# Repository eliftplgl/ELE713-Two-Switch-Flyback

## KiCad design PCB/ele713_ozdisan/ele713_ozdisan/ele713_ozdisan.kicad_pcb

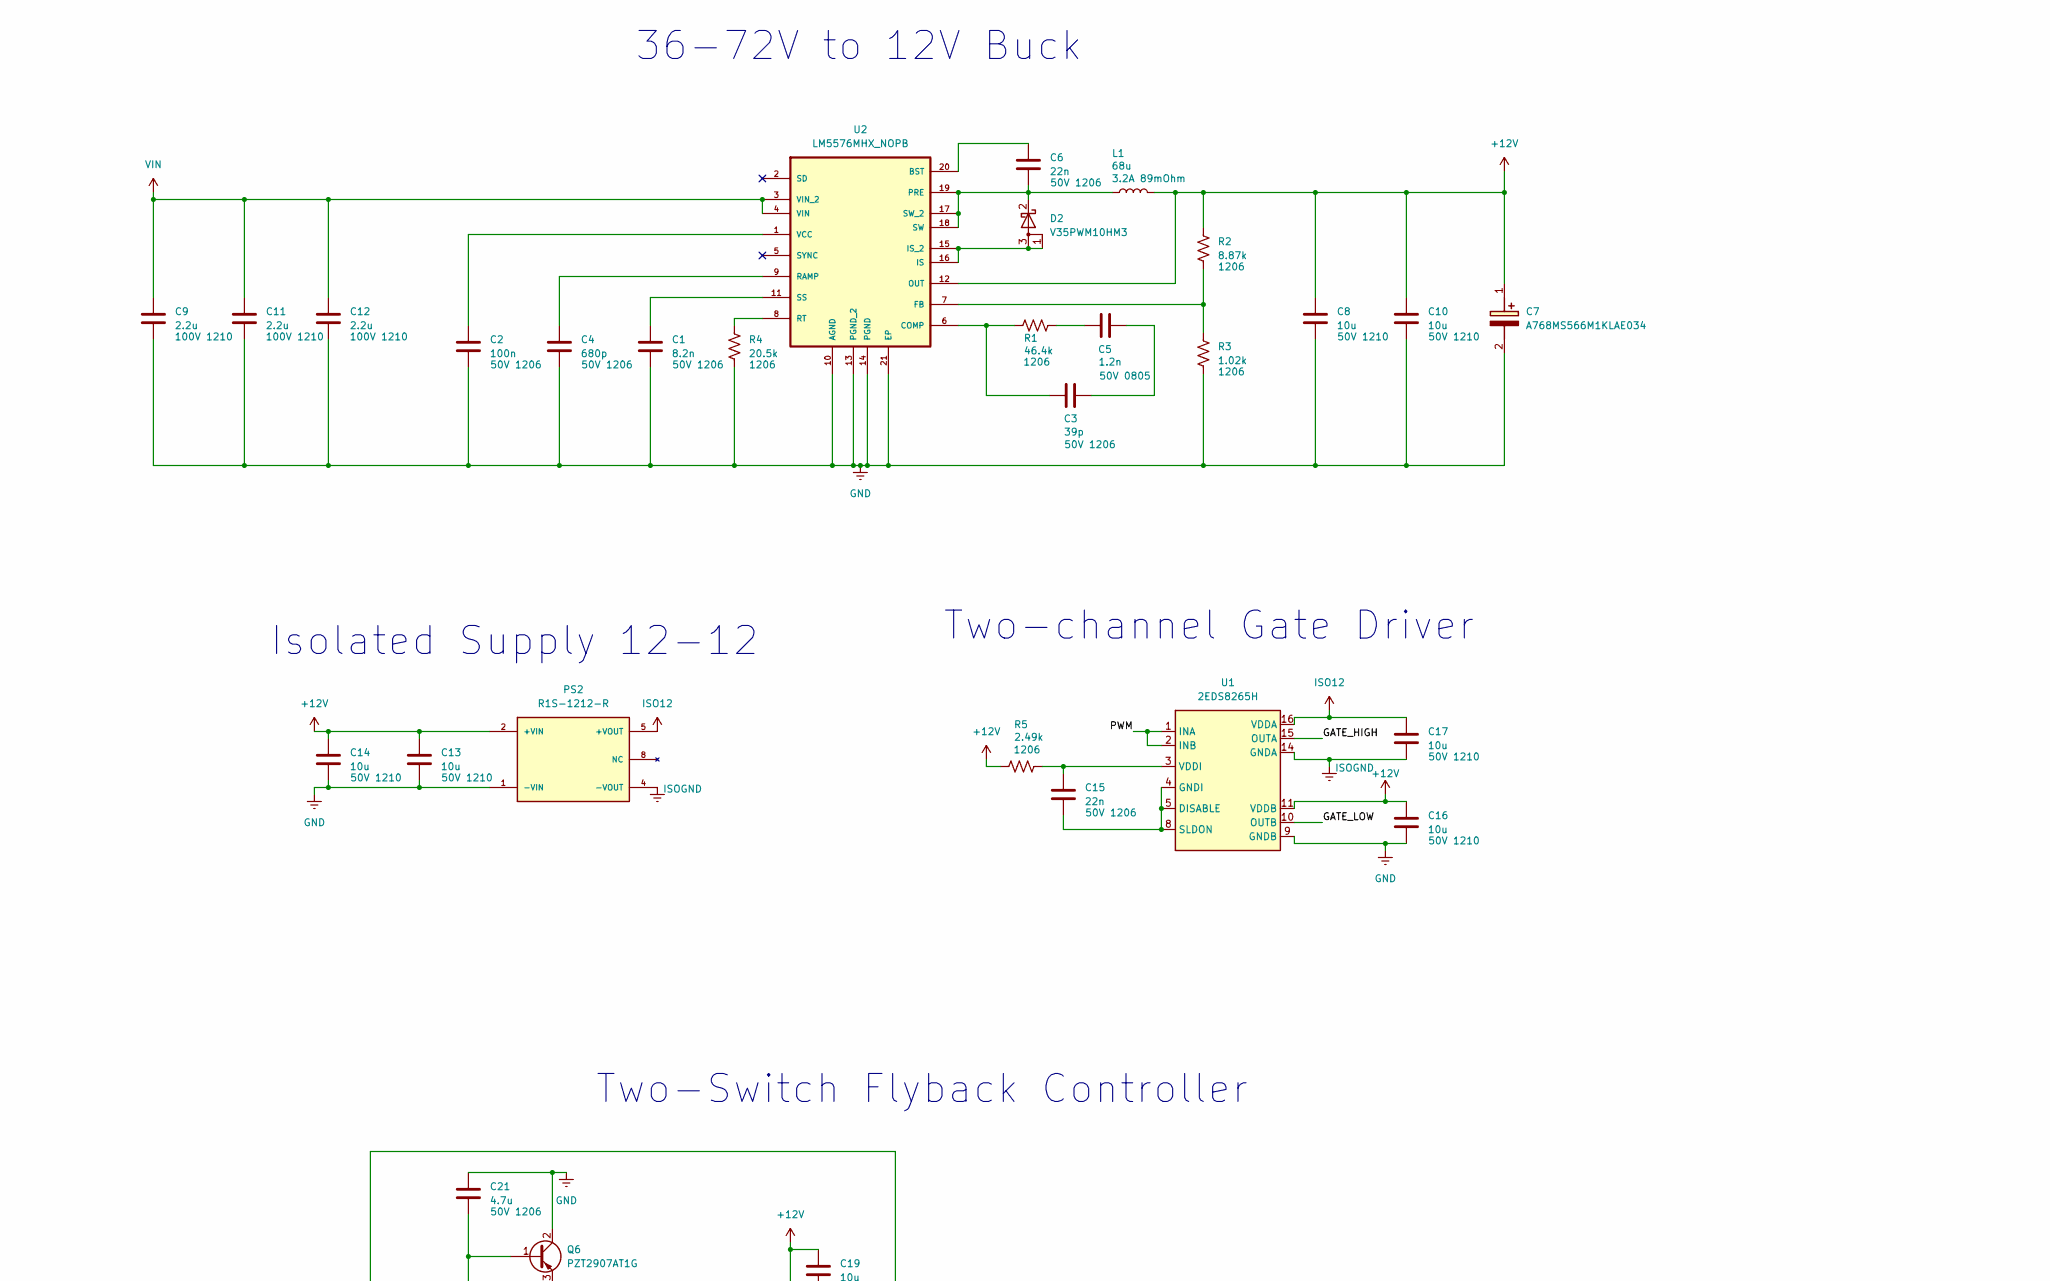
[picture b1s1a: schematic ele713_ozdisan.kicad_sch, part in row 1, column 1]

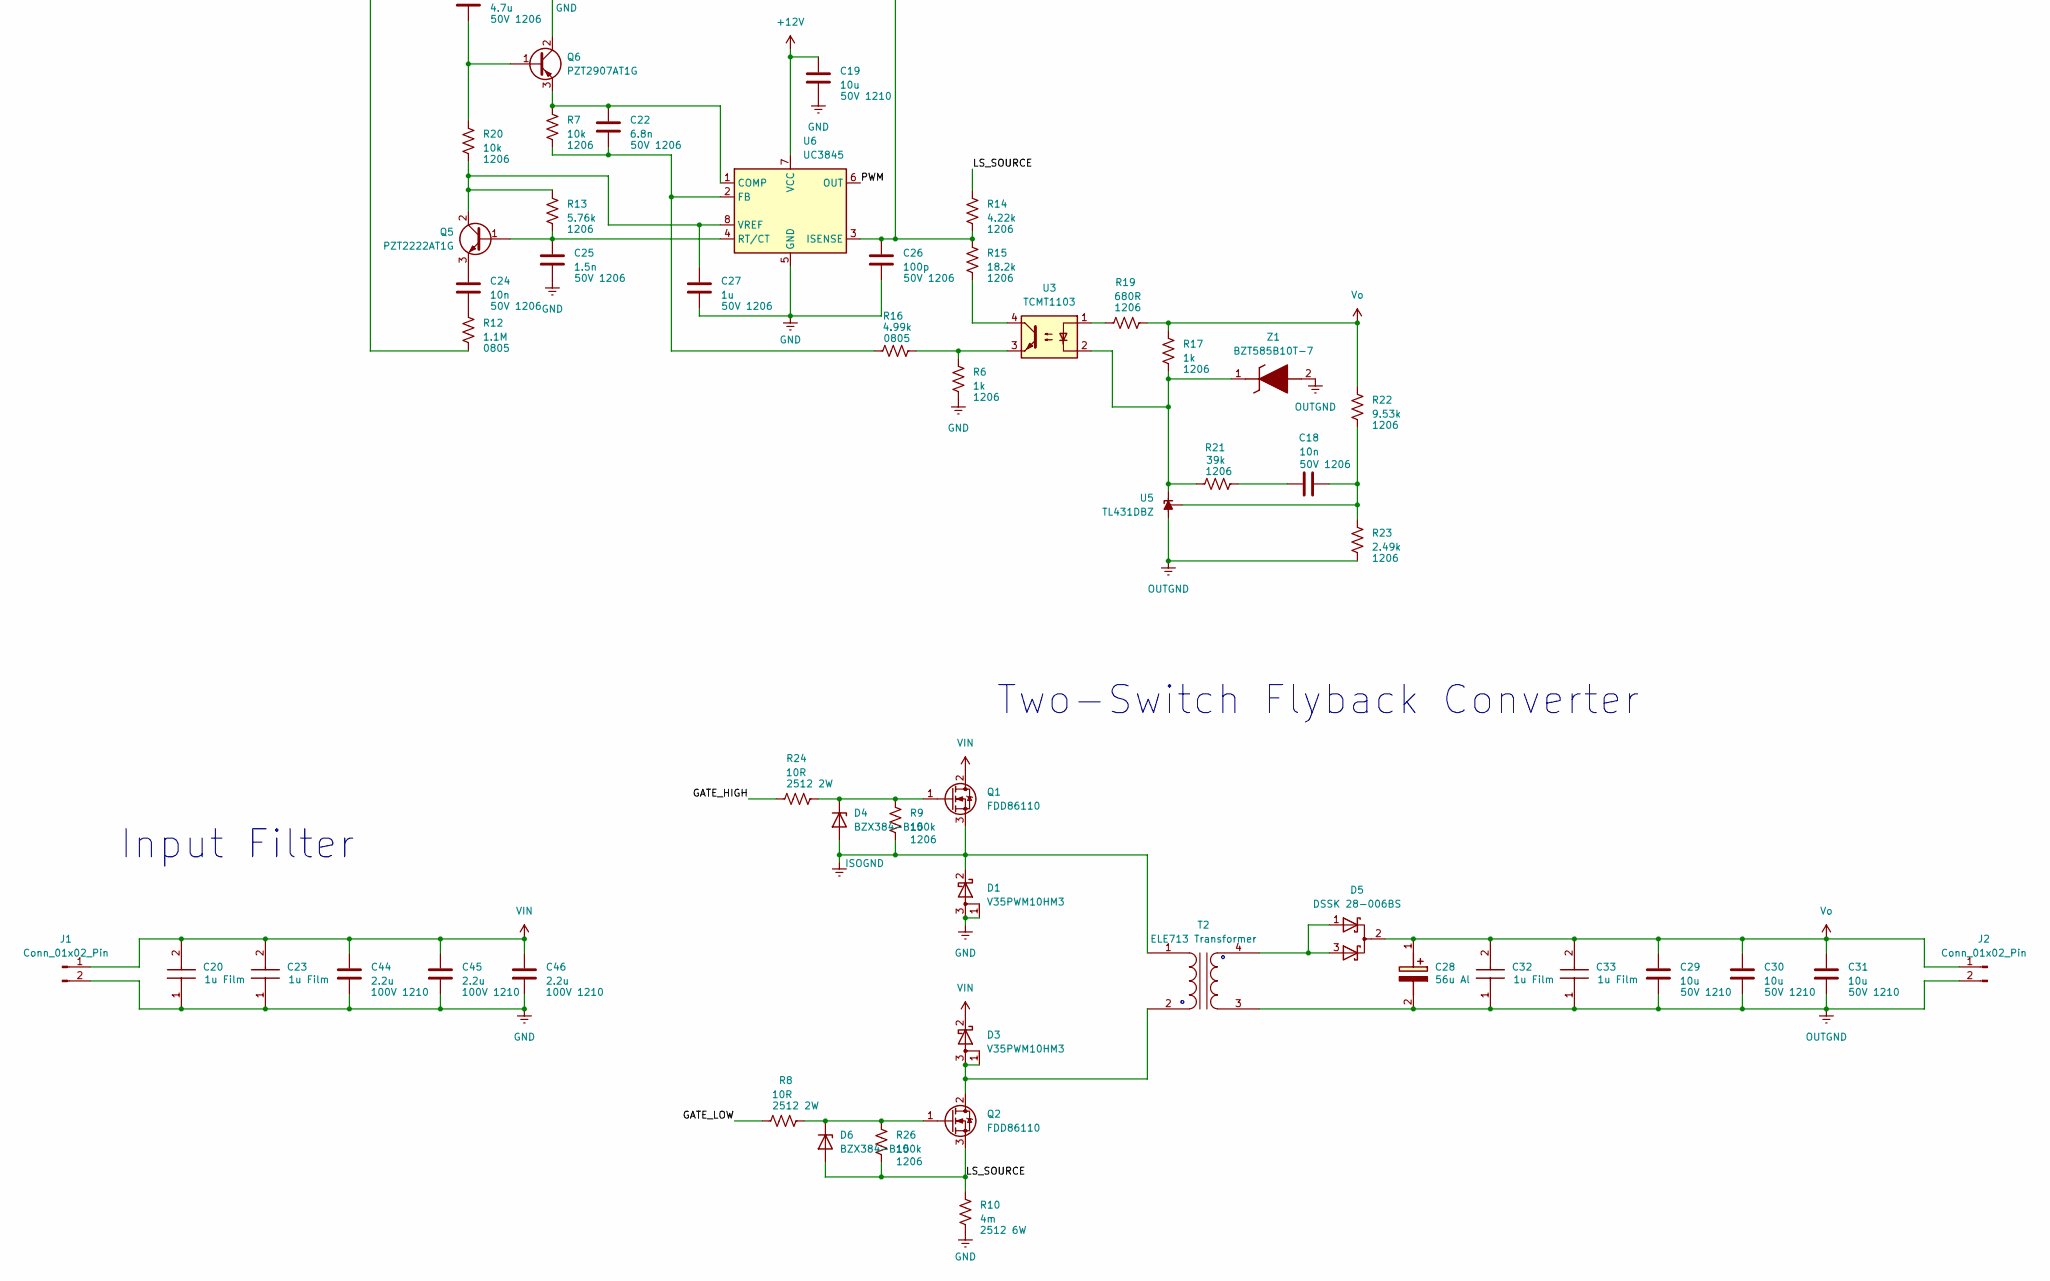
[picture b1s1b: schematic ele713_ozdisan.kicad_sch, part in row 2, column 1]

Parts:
C1: 8.2n; C_1206_3216Metric_Pad1.33x1.80mm_HandSolder
C2: 100n; C_1206_3216Metric_Pad1.33x1.80mm_HandSolder
C3: 39p; C_1206_3216Metric_Pad1.33x1.80mm_HandSolder
C4: 680p; C_1206_3216Metric_Pad1.33x1.80mm_HandSolder
C5: 1.2n; C_0805_2012Metric_Pad1.18x1.45mm_HandSolder
C6, C15: 22n; C_1206_3216Metric_Pad1.33x1.80mm_HandSolder
C7, C28: A768MS566M1KLAE034; CAPAE1030X1270N; Manufacturer_Part_Number A768MS566M1KLAE034; Mouser Part Number 80-A768MS566M1KLAE34
C8, C10, C13, C14, C16, C17, C19, C29, C30, C31: 10u; C_1210_3225Metric_Pad1.33x2.70mm_HandSolder
C9, C11, C12, C44, C45, C46: 2.2u; C_1210_3225Metric_Pad1.33x2.70mm_HandSolder
C18, C24: 10n; C_1206_3216Metric_Pad1.33x1.80mm_HandSolder
C20, C23, C32, C33: R82EC4100DQ70J; Manufacturer_Part_Number R82EC4100DQ70J; Mouser Part Number 80-R82EC4100DQ70J
C21: 4.7u; C_1206_3216Metric_Pad1.33x1.80mm_HandSolder
C22: 6.8n; C_1206_3216Metric_Pad1.33x1.80mm_HandSolder
C25: 1.5n; C_1206_3216Metric_Pad1.33x1.80mm_HandSolder
C26: 100p; C_1206_3216Metric_Pad1.33x1.80mm_HandSolder
C27: 1u; C_1206_3216Metric_Pad1.33x1.80mm_HandSolder
D1, D2, D3: V35PWM10HM3; TO-252-2
D4, D6: BZX384-B15; D_SOD-323_HandSoldering
D5: DSSK 28-006BS; TO-263-2
J1, J2: Conn_01x02_Pin; TerminalBlock_Phoenix_MKDS-1,5-2_1x02_P5.00mm_Horizontal
L1: 68u; WE-PD_1210
PS2: R1S-1212-R; CONV_R1S-1212-R; PARTREV 1; DigiKey_Part_Number 945-1017-2-ND
Q1, Q2: FDD86110; TO-252-2
Q5: PZT2222AT1G; SOT-223-3_TabPin2
Q6: PZT2907AT1G; SOT-223-3_TabPin2
R1: 46.4k; R_1206_3216Metric_Pad1.30x1.75mm_HandSolder
R2: 8.87k; R_1206_3216Metric_Pad1.30x1.75mm_HandSolder
R3: 1.02k; R_1206_3216Metric_Pad1.30x1.75mm_HandSolder
R4: 20.5k; R_1206_3216Metric_Pad1.30x1.75mm_HandSolder
R5, R23: 2.49k; R_1206_3216Metric_Pad1.30x1.75mm_HandSolder
R6, R17: 1k; R_1206_3216Metric_Pad1.30x1.75mm_HandSolder
R7, R20: 10k; R_1206_3216Metric_Pad1.30x1.75mm_HandSolder
R8, R24: 10R; D_2512_6332Metric_Pad1.52x3.35mm_HandSolder
R9, R26: 100k; R_1206_3216Metric_Pad1.30x1.75mm_HandSolder
R10: 4m; R_2512_6332Metric_Pad1.40x3.35mm_HandSolder
R12: 1.1M; R_0805_2012Metric_Pad1.20x1.40mm_HandSolder
R13: 5.76k; R_1206_3216Metric_Pad1.30x1.75mm_HandSolder
R14: 4.22k; R_1206_3216Metric_Pad1.30x1.75mm_HandSolder
R15: 18.2k; R_1206_3216Metric_Pad1.30x1.75mm_HandSolder
R16: 4.99k; R_0805_2012Metric_Pad1.20x1.40mm_HandSolder
R19: 680R; R_1206_3216Metric_Pad1.30x1.75mm_HandSolder
R21: 39k; R_1206_3216Metric_Pad1.30x1.75mm_HandSolder
R22: 9.53k; R_1206_3216Metric_Pad1.30x1.75mm_HandSolder
T2: ELE713 Transformer; ETD39_coilformer
U1: 2EDS8265H; SOIC-16_3.9x9.9mm_P1.27mm
U2: LM5576MHX_NOPB; SOP65P640X110-21N; MPN LM5576MHX/NOPB
U3: TCMT1103; SOP-4_4.4x2.6mm_P1.27mm
U5: TL431DBZ; SOT-23_Handsoldering
U6: UC3845; SOIC127P599X175-8N
Z1: BZT585B10T-7; SODFL1608X65N; Manufacturer_Part_Number BZT585B10T-7; Mouser Part Number 621-BZT585B10T-7

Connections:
+12V: C7.1 (+), C8.1, C10.1, C13.1, C14.1, C16.1, C19.1, L1.2, PS2.2 (+VIN), R2.1, R5.1, U1.11 (VDDB), U2.12 (OUT), U6.7 (VCC)
/GATE_HIGH: R24.1, U1.15 (OUTA)
/GATE_LOW: R8.1, U1.10 (OUTB)
/LS_SOURCE: D6.2 (A), Q2.3 (S), R10.1, R14.1, R26.2
/PWM: U1.1 (INA), U1.2 (INB), U6.6 (OUT)
GND: C1.2, C2.2, C4.2, C7.2 (-), C8.2, C9.2, C10.2, C11.2, C12.2, C13.2, C14.2, C16.2, C19.2, C20.1, C21.1, C23.1, C25.2, C26.2, C27.2, C44.2, C45.2, C46.2, D1.1 (A), D1.3 (A), J1.2, PS2.1 (-VIN), Q6.2 (C), R3.2, R4.2, R6.2, R10.2, U1.9 (GNDB), U2.10 (AGND), U2.13 (PGND_2), U2.14 (PGND), U2.21 (EP), U6.5 (GND)
ISO12: C17.1, PS2.5 (+VOUT), U1.16 (VDDA)
ISOGND: C17.2, D1.2 (K), D4.2 (A), PS2.4 (-VOUT), Q1.3 (S), R9.2, T2.1 (AA), U1.14 (GNDA)
unnamed: C3.2, C5.2
unnamed: C5.1, R1.2
unnamed: C18.1, R21.2
unnamed: C24.2, R12.1
unnamed: C6.2, D2.2 (K), L1.1, U2.17 (SW_2), U2.18 (SW), U2.19 (PRE)
unnamed: D4.1 (K), Q1.1 (G), R9.1, R24.2
unnamed: D6.1 (K), Q2.1 (G), R8.2, R26.1
unnamed: C25.1, Q5.1 (B), R13.2, U6.4 (RT/CT)
unnamed: C27.1, Q5.2 (C), R13.1, R20.2, U6.8 (VREF)
unnamed: C24.1, Q5.3 (E)
unnamed: C21.2, Q6.1 (B), R20.1
unnamed: C22.1, Q6.3 (E), R7.1, U6.1 (COMP)
unnamed: R15.2, U3.4
unnamed: R6.1, R16.2, U3.3
unnamed: R19.1, U3.1
unnamed: D3.1 (A), D3.3 (A), Q2.2 (D), T2.2 (AB)
unnamed: D5.1 (A), D5.3 (A), T2.4 (SB)
unnamed: C15.2, U1.4 (GNDI), U1.5 (DISABLE), U1.8 (SLDON)
unnamed: C15.1, R5.2, U1.3 (VDDI)
unnamed: C6.1, U2.20 (BST)
unnamed: C3.1, R1.1, U2.6 (COMP)
unnamed: R2.2, R3.1, U2.7 (FB)
unnamed: D2.1 (A), D2.3 (A), U2.15 (IS_2), U2.16 (IS)
unnamed: C4.1, U2.9 (RAMP)
unnamed: R4.1, U2.8 (RT)
unnamed: C1.1, U2.11 (SS)
unnamed: C2.1, U2.1 (VCC)
unnamed: R17.2, R21.1, U3.2, U5.1 (K), Z1.1 (K)
unnamed: C18.2, R22.2, R23.1, U5.2 (REF)
unnamed: C22.2, R7.2, R16.1, U6.2 (FB)
unnamed: C26.1, R12.2, R14.2, R15.1, U6.3 (ISENSE)
OUTGND: C28.2 (-), C29.2, C30.2, C31.2, C32.1, C33.1, J2.2, R23.2, T2.3 (SA), U5.3 (A), Z1.2 (A)
VIN: C9.1, C11.1, C12.1, C20.2, C23.2, C44.1, C45.1, C46.1, D3.2 (K), J1.1, Q1.2 (D), U2.3 (VIN_2), U2.4 (VIN)
Vo: C28.1 (+), C29.1, C30.1, C31.1, C32.2, C33.2, D5.2 (K), J2.1, R17.1, R19.2, R22.1

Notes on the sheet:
Isolated Supply 12-12
Two-Switch Flyback Converter
Two-Switch Flyback Controller
36-72V to 12V Buck
Two-channel Gate Driver
Input Filter

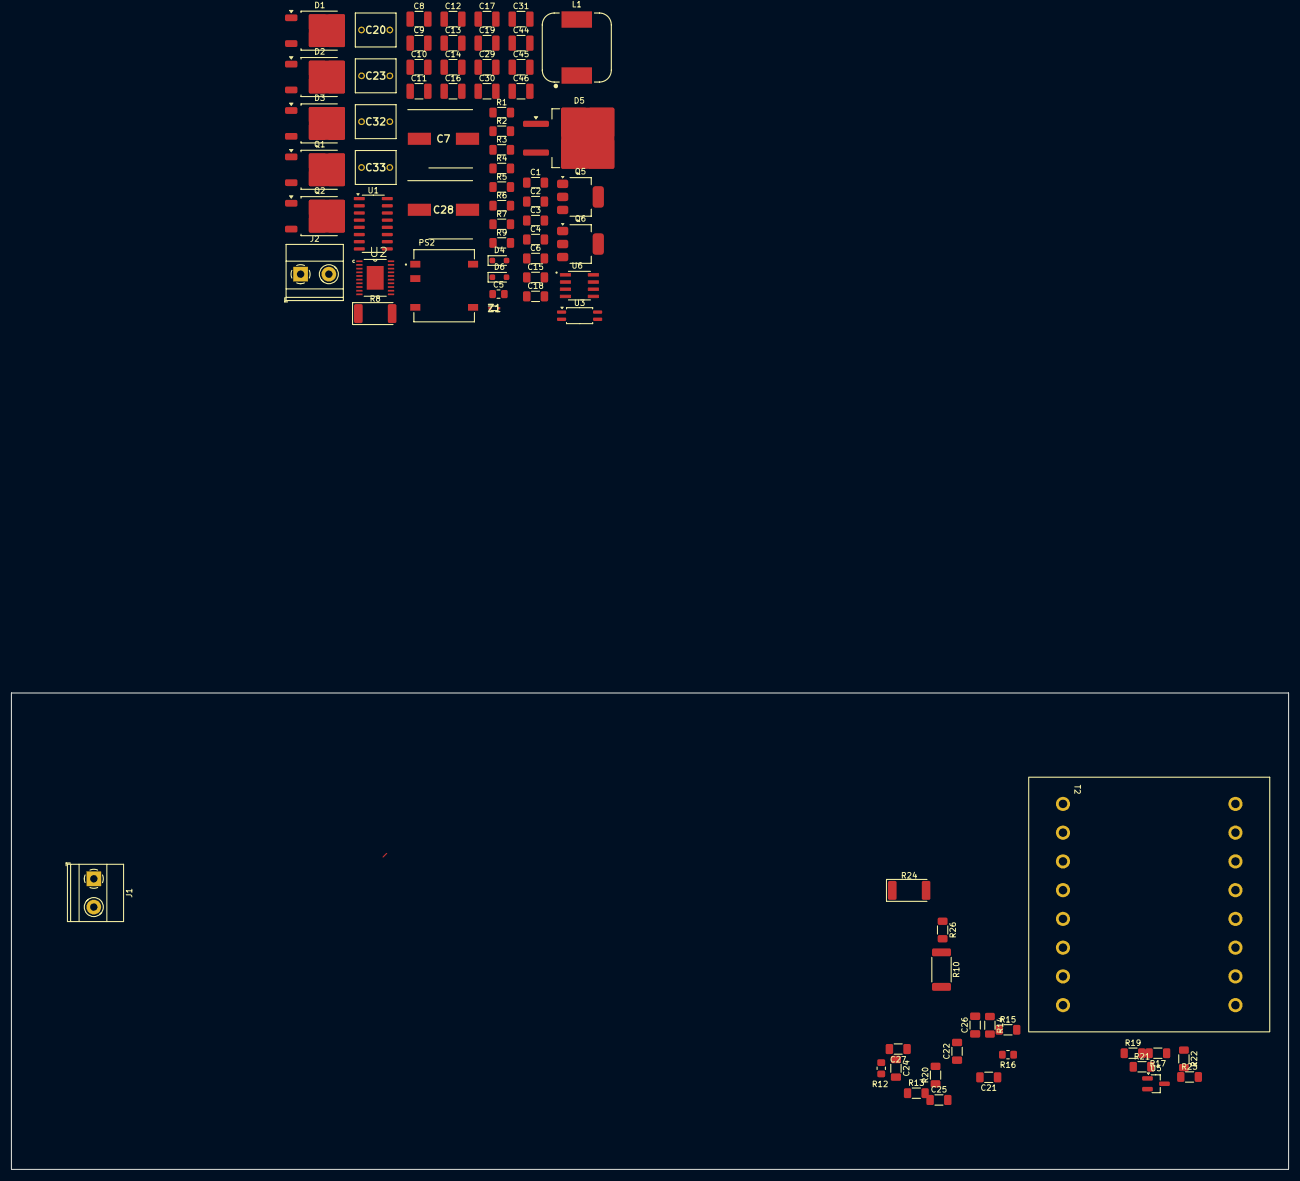
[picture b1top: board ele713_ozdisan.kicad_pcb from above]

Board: 2 copper layers, 225.7 x 84.2 mm, 80 parts (0 on the bottom side), 42 nets.

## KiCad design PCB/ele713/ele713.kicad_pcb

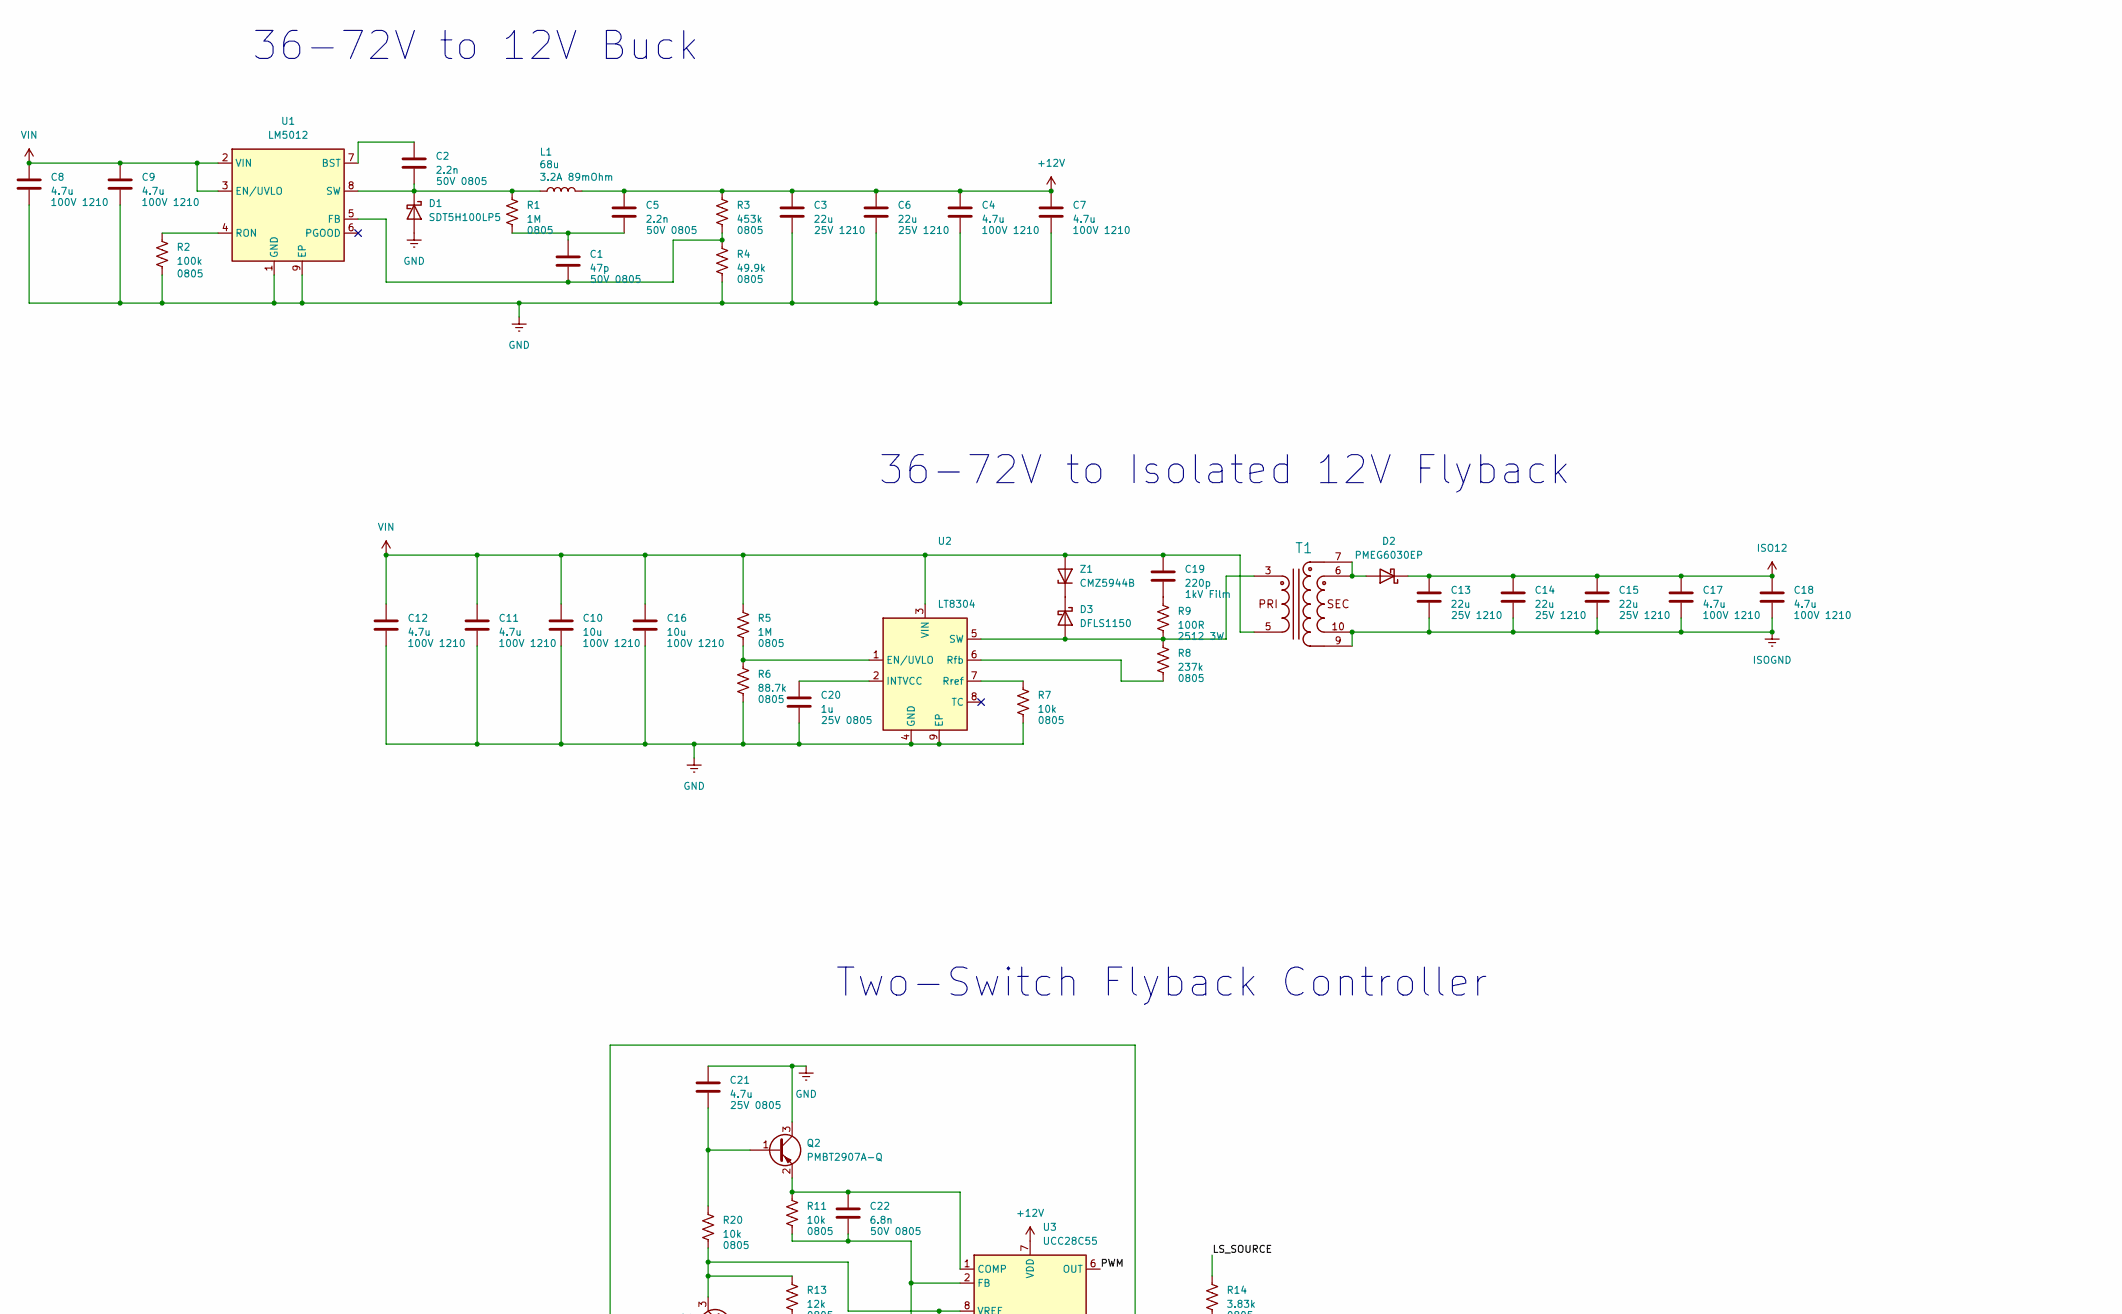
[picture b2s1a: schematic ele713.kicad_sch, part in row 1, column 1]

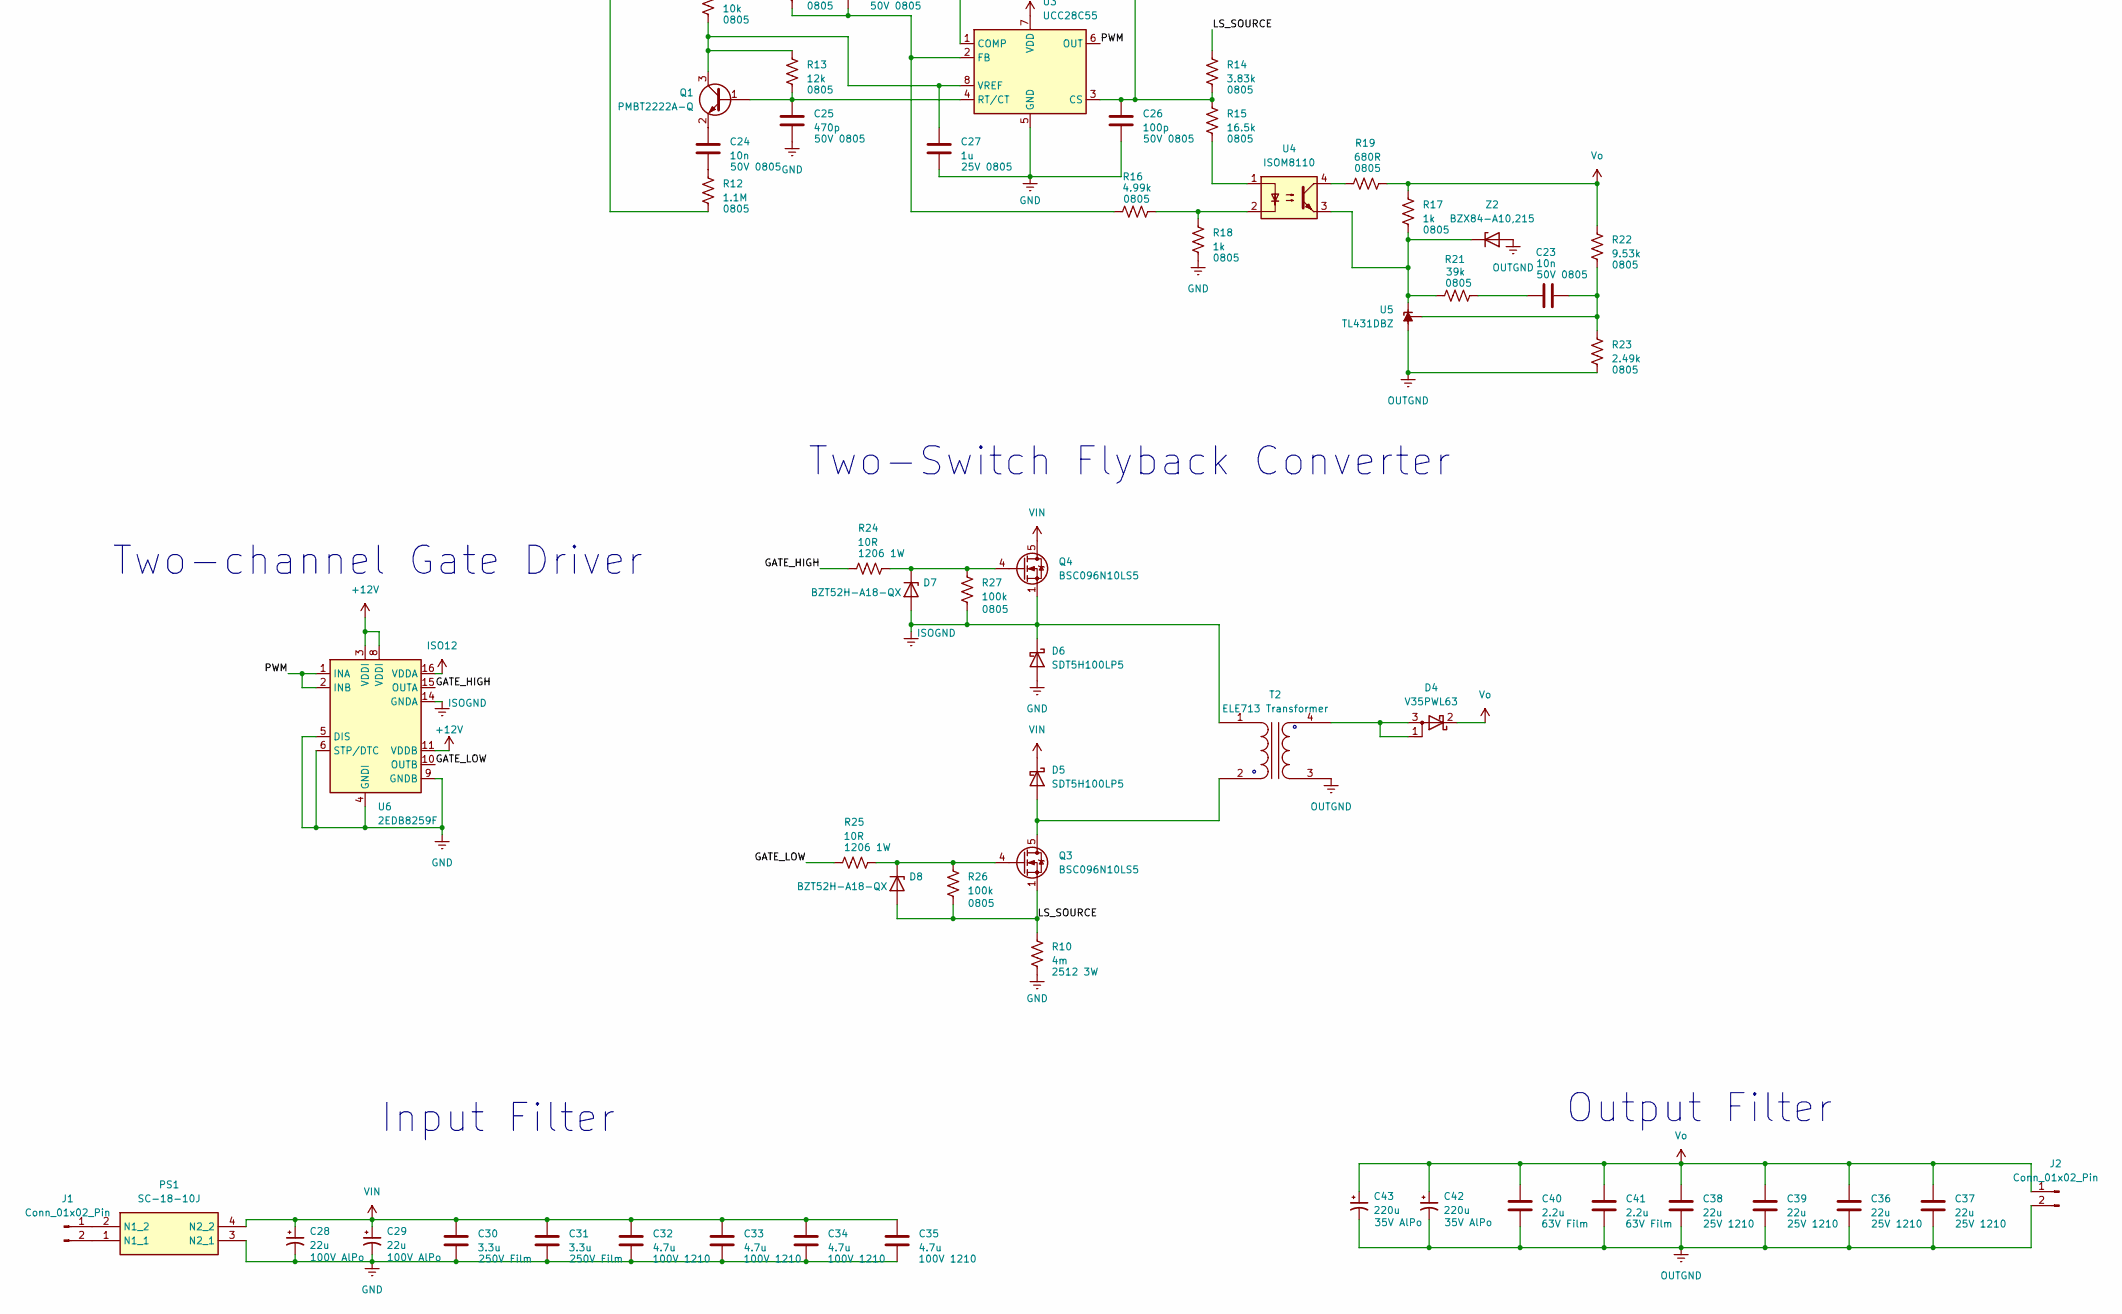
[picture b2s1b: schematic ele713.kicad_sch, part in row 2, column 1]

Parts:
C1: 47p; C_0805_2012Metric_Pad1.18x1.45mm_HandSolder
C2, C5: 2.2n; C_0805_2012Metric_Pad1.18x1.45mm_HandSolder
C3, C6, C13, C14, C15, C36, C37, C38, C39: 22u; C_1210_3225Metric_Pad1.33x2.70mm_HandSolder
C4, C7, C8, C9, C11, C12, C17, C18, C32, C33, C34, C35: 4.7u; C_1210_3225Metric_Pad1.33x2.70mm_HandSolder
C10, C16: 10u; C_1210_3225Metric_Pad1.33x2.70mm_HandSolder
C19: 220p; R76QD0220SE00J
C20, C27: 1u; C_0805_2012Metric_Pad1.18x1.45mm_HandSolder
C21: 4.7u; C_0805_2012Metric_Pad1.18x1.45mm_HandSolder
C22: 6.8n; C_0805_2012Metric_Pad1.18x1.45mm_HandSolder
C23, C24: 10n; C_0805_2012Metric_Pad1.18x1.45mm_HandSolder
C25: 470p; C_0805_2012Metric_Pad1.18x1.45mm_HandSolder
C26: 100p; C_0805_2012Metric_Pad1.18x1.45mm_HandSolder
C28, C29: 22u; CP_Radial_D10.0mm_P5.00mm
C30, C31: 3.3u; R46KN410050N1K
C40, C41: 2.2u; F861KM473M310A
C42, C43: 220u; CAPAE830X1250N
D1, D5, D6: SDT5H100LP5; D_PowerDI-5
D2: PMEG6030EP; D_SOD-128
D3: DFLS1150; D_PowerDI-123
D4: V35PWL63; TO-252-2
D7, D8: BZT52H-A18-QX; D_SOD-123F
J1, J2: Conn_01x02_Pin; TerminalBlock_RND_205-00067_1x02_P7.50mm_Horizontal
L1: 68u; L_Coilcraft_MSS1210-XXX
PS1: SC-18-10J; SC1810J; Manufacturer_Part_Number SC-18-10J; Mouser Part Number 80-SC-18-10J
Q1: PMBT2222A-Q; SOT-23_Handsoldering
Q2: PMBT2907A-Q; SOT-23_Handsoldering
Q3, Q4: BSC096N10LS5; TDSON-8-1
R1, R5: 1M; R_0805_2012Metric_Pad1.20x1.40mm_HandSolder
R2, R26, R27: 100k; R_0805_2012Metric_Pad1.20x1.40mm_HandSolder
R3: 453k; R_0805_2012Metric_Pad1.20x1.40mm_HandSolder
R4: 49.9k; R_0805_2012Metric_Pad1.20x1.40mm_HandSolder
R6: 88.7k; R_0805_2012Metric_Pad1.20x1.40mm_HandSolder
R7, R11, R20: 10k; R_0805_2012Metric_Pad1.20x1.40mm_HandSolder
R8: 237k; R_0805_2012Metric_Pad1.20x1.40mm_HandSolder
R9: 100R; R_2512_6332Metric_Pad1.40x3.35mm_HandSolder
R10: 4m; R_2512_6332Metric_Pad1.40x3.35mm_HandSolder
R12: 1.1M; R_0805_2012Metric_Pad1.20x1.40mm_HandSolder
R13: 12k; R_0805_2012Metric_Pad1.20x1.40mm_HandSolder
R14: 3.83k; R_0805_2012Metric_Pad1.20x1.40mm_HandSolder
R15: 16.5k; R_0805_2012Metric_Pad1.20x1.40mm_HandSolder
R16: 4.99k; R_0805_2012Metric_Pad1.20x1.40mm_HandSolder
R17, R18: 1k; R_0805_2012Metric_Pad1.20x1.40mm_HandSolder
R19: 680R; R_0805_2012Metric_Pad1.20x1.40mm_HandSolder
R21: 39k; R_0805_2012Metric_Pad1.20x1.40mm_HandSolder
R22: 9.53k; R_0805_2012Metric_Pad1.20x1.40mm_HandSolder
R23: 2.49k; R_0805_2012Metric_Pad1.20x1.40mm_HandSolder
R24, R25: 10R; D_1206_3216Metric_Pad1.42x1.75mm_HandSolder
T1: Vi = 36-72V, Vo = 12V / 1.25A; WE-FLYLT_EP13_L13.46W17.75H12.70; Input Voltage 36-72VDC; Output Voltage 1 12V; Manufacturer Part Number 750315126
T2: ELE713 Transformer; ETD39_coilformer
U1: LM5012; HSOP-8-1EP_3.9x4.9mm_P1.27mm_EP2.41x3.1mm_ThermalVias
U2: LT8304; SOIC-8-1EP_3.9x4.9mm_P1.27mm_EP2.29x3mm
U3: UCC28C55; VSSOP-8_3x3mm_P0.65mm
U4: ISOM8110; SOIC-4_4.55x3.7mm_P2.54mm
U5: TL431DBZ; SOT-23
U6: 2EDB8259F; SOIC-16_3.9x9.9mm_P1.27mm
Z1: CMZ5944B; D_SMA_Handsoldering
Z2: BZX84-A10,215; SOT-23_Handsoldering

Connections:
+12V: C3.1, C4.1, C5.1, C6.1, C7.1, L1.2, R3.1, U3.7 (VDD), U6.3 (VDDI), U6.8 (VDDI), U6.11 (VDDB)
/GATE_HIGH: R24.1, U6.15 (OUTA)
/GATE_LOW: R25.1, U6.10 (OUTB)
/LS_SOURCE: D8.2 (A), Q3.1 (S), Q3.2 (S), Q3.3 (S), R10.1, R14.1, R26.2
/PWM: U3.6 (OUT), U6.1 (INA), U6.2 (INB)
GND: C3.2, C4.2, C6.2, C7.2, C8.2, C9.2, C10.2, C11.2, C12.2, C16.2, C20.2, C21.1, C25.2, C26.2, C27.2, C28.2, C29.2, C30.2, C31.2, C32.2, C33.2, C34.2, C35.2, D1.2 (A), D6.2 (A), PS1.3 (N2_1), Q2.3 (C), R2.2, R4.2, R6.2, R7.2, R10.2, R18.2, U1.1 (GND), U1.9 (EP), U2.4 (GND), U2.9 (EP), U3.5 (GND), U6.4 (GNDI), U6.5 (DIS), U6.6 (STP/DTC), U6.9 (GNDB)
ISO12: C13.1, C14.1, C15.1, C17.1, C18.1, D2.1 (K), U6.16 (VDDA)
ISOGND: C13.2, C14.2, C15.2, C17.2, C18.2, D6.1 (K), D7.2 (A), Q4.1 (S), Q4.2 (S), Q4.3 (S), R27.2, T1.9, T1.10, T2.1 (AA), U6.14 (GNDA)
unnamed: C1.1, C5.2, R1.2
unnamed: C19.2, R9.1
unnamed: C23.1, R21.2
unnamed: C24.2, R12.1
unnamed: C2.2, D1.1 (K), L1.1, R1.1, U1.8 (SW)
unnamed: D2.2 (A), T1.6, T1.7
unnamed: D3.2 (A), R8.1, R9.2, T1.3, U2.5 (SW)
unnamed: D3.1 (K), Z1.1 (K)
unnamed: D5.2 (A), Q3.5 (D), T2.2 (AB)
unnamed: D7.1 (K), Q4.4 (G), R24.2, R27.1
unnamed: D8.1 (K), Q3.4 (G), R25.2, R26.1
unnamed: J1.1, PS1.2 (N1_2)
unnamed: J1.2, PS1.1 (N1_1)
unnamed: C25.1, Q1.1 (B), R13.2, U3.4 (RT/CT)
unnamed: C27.1, Q1.3 (C), R13.1, R20.2, U3.8 (VREF)
unnamed: C24.1, Q1.2 (E)
unnamed: C21.2, Q2.1 (B), R20.1
unnamed: C22.1, Q2.2 (E), R11.1, U3.1 (COMP)
unnamed: R15.2, U4.1
unnamed: R16.2, R18.1, U4.2
unnamed: R19.1, U4.4
unnamed: D4.1 (A), D4.3 (A), T2.4 (SB)
unnamed: C2.1, U1.7 (BST)
unnamed: C1.2, R3.2, R4.1, U1.5 (FB)
unnamed: R2.1, U1.4 (RON)
unnamed: R5.2, R6.1, U2.1 (EN/UVLO)
unnamed: C20.1, U2.2 (INTVCC)
unnamed: R8.2, U2.6 (Rfb)
unnamed: R7.1, U2.7 (Rref)
unnamed: C26.1, R12.2, R14.2, R15.1, U3.3 (CS)
unnamed: C22.2, R11.2, R16.1, U3.2 (FB)
unnamed: R17.2, R21.1, U4.3, U5.1 (K), Z2.3 (K)
unnamed: C23.2, R22.2, R23.1, U5.2 (REF)
OUTGND: C36.2, C37.2, C38.2, C39.2, C40.2, C41.2, C42.2, C43.2, J2.2, R23.2, T2.3 (SA), U5.3 (A), Z2.1 (A)
VIN: C8.1, C9.1, C10.1, C11.1, C12.1, C16.1, C19.1, C28.1, C29.1, C30.1, C31.1, C32.1, C33.1, C34.1, C35.1, D5.1 (K), PS1.4 (N2_2), Q4.5 (D), R5.1, T1.5, U1.2 (VIN), U1.3 (EN/UVLO), U2.3 (VIN), Z1.2 (A)
Vo: C36.1, C37.1, C38.1, C39.1, C40.1, C41.1, C42.1, C43.1, D4.2 (K), J2.1, R17.1, R19.2, R22.1

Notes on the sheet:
Two-Switch Flyback Converter
Output Filter
36-72V to Isolated 12V Flyback
Two-Switch Flyback Controller
36-72V to 12V Buck
Two-channel Gate Driver
Input Filter

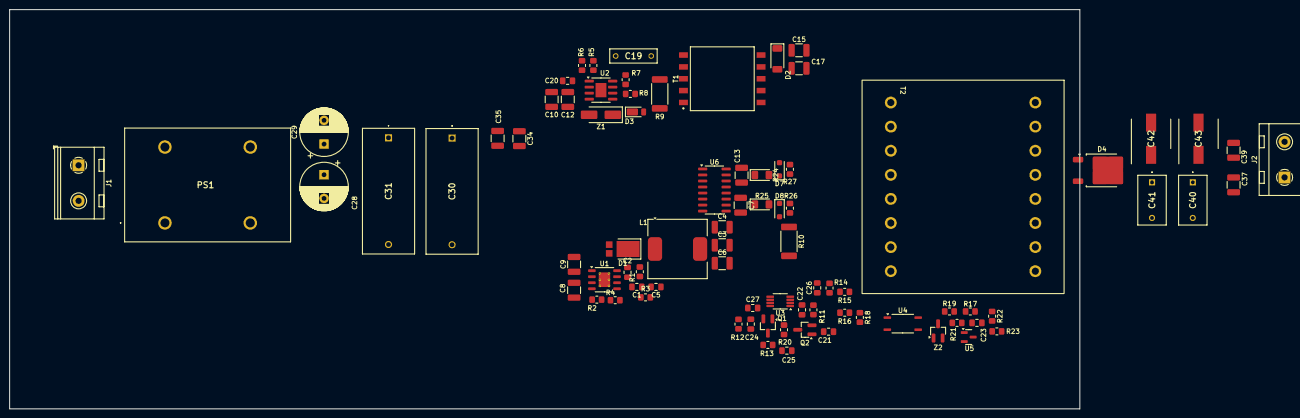
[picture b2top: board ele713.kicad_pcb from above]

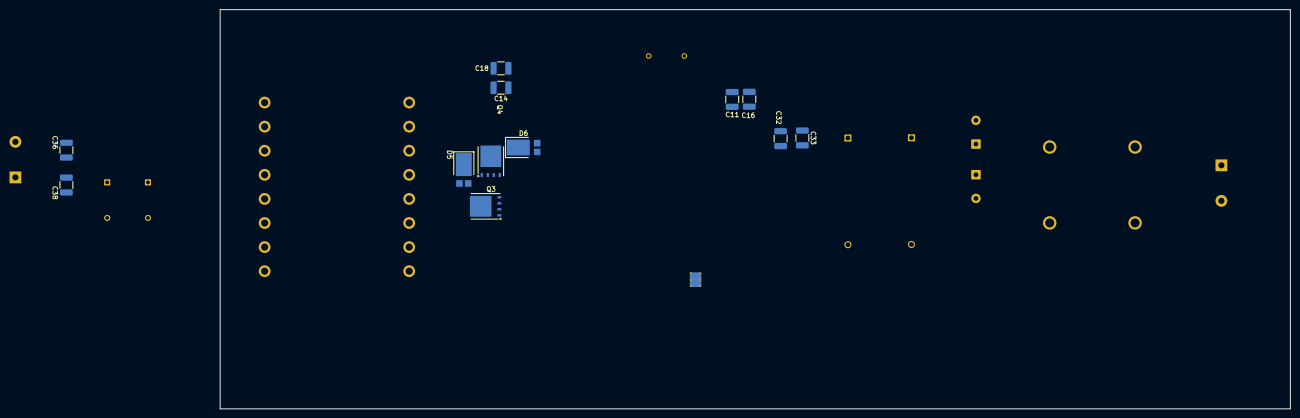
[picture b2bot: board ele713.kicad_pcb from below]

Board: 2 copper layers, 225.7 x 84.2 mm, 96 parts (12 on the bottom side), 44 nets.

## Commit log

2024-11-25 Flyback design tool V1
2024-11-25 Component List and Simulation Files were added
2024-11-30 Controller design parameters
2024-11-30 simulation ltspice
2024-12-01 Component List almost done, input and output filters left
2024-12-02 Final component list with mostly exact component counts
2024-12-10 Controller schematics done, though some lib files only exist on lab computer
2024-12-11 libraries added, schematic fully completed except terminals
2024-12-17 pcb v1 is uploaded
2024-12-23 digikey -> ozdisan half done. magenta ones are OK, green ones need work
2024-12-24 almost done digikey -> ozdisan, orange ones are unfinished. red ones are critical
2024-12-24 only optocoupler missing
2024-12-31 ozdisan version schematic finished
2025-01-03 PCB v1 ve v2 çizildi
    Çok sancılı bir süreç, ilk PCB yi çizmek zormuş yıprandım. Neyse, v1 ve v2 çizildi. V2 basılacak olan şimdilik.
2025-01-16 closed loop simulation
2025-01-16 report v1
